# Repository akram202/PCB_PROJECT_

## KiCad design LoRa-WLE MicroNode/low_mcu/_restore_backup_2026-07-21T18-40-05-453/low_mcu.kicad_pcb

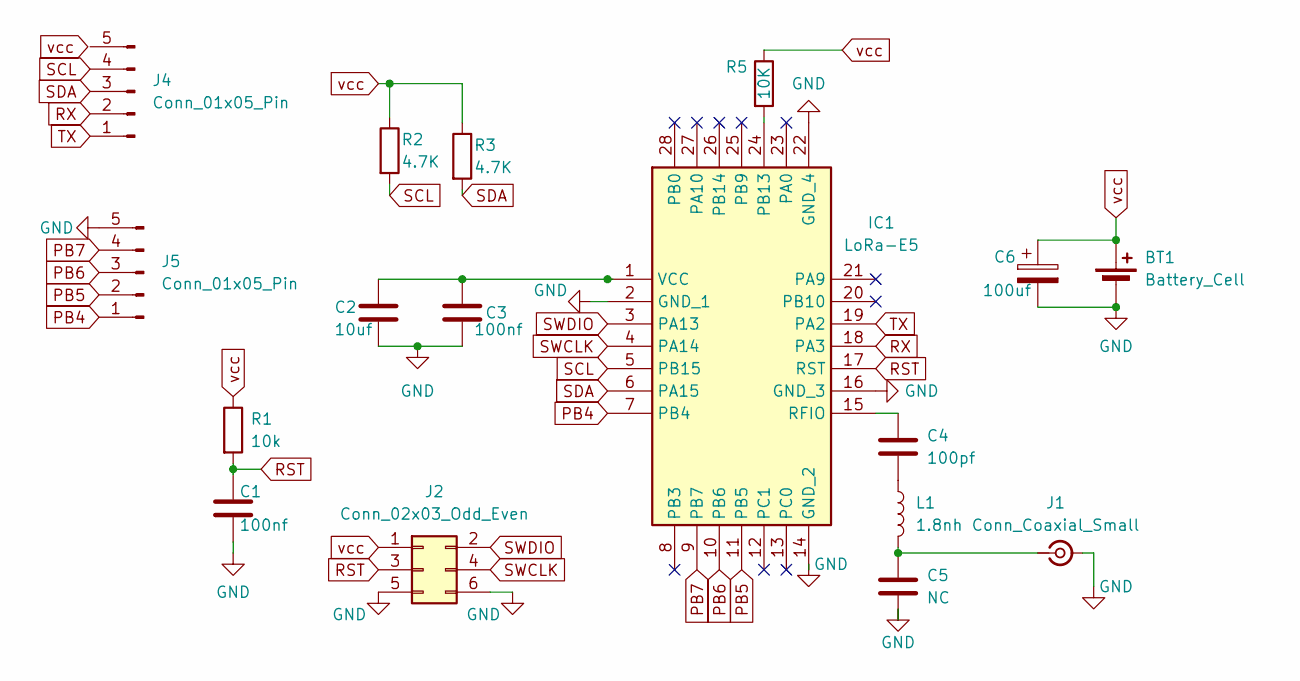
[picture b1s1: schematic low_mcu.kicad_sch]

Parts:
BT1: Battery_Cell; BatteryHolder_Keystone_3002_1x2032
C1, C3: 100nf; C_0402_1005Metric_Pad0.74x0.62mm_HandSolder
C2: 10uf; C_0603_1608Metric
C4: 100pf; C_0402_1005Metric
C5: NC; C_0402_1005Metric
C6: 100uf; CP_EIA-3528-21_Kemet-B
IC1: LoRa-E5; LoRaE5; Manufacturer_Part_Number LoRa-E5
J1: Conn_Coaxial_Small; U.FL_Hirose_U.FL-R-SMT-1_Vertical
J2: Conn_02x03_Odd_Even; Tag-Connect_TC2030-IDC-FP_2x03_P1.27mm_Vertical
J4, J5: Conn_01x05_Pin; PinHeader_1x05_P2.54mm_Vertical
L1: 1.8nh; L_0402_1005Metric
R1: 10k; R_0402_1005Metric
R2, R3: 4.7K; R_01005_0402Metric
R5: 10K; R_0402_1005Metric

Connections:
GND: BT1.2 (-), C1.2, C2.2, C3.2, C5.2, C6.2, IC1.2 (GND_1), IC1.14 (GND_2), IC1.16 (GND_3), IC1.22 (GND_4), J1.2 (Ext), J2.5, J2.6, J5.5
unnamed: C4.2, L1.1
unnamed: IC1.24 (PB13), R5.2
unnamed: C4.1, IC1.15 (RFIO)
unnamed: C2.1, C3.1, IC1.1 (VCC)
unnamed: C5.1, J1.1 (In), L1.2
PB4: IC1.7 (PB4), J5.1
PB5: IC1.11 (PB5), J5.2
PB6: IC1.10 (PB6), J5.3
PB7: IC1.9 (PB7), J5.4
RST: C1.1, IC1.17 (RST), J2.3, R1.2
RX: IC1.18 (PA3), J4.2
SCL: IC1.5 (PB15), J4.4, R2.2
SDA: IC1.6 (PA15), J4.3, R3.2
SWCLK: IC1.4 (PA14), J2.4
SWDIO: IC1.3 (PA13), J2.2
TX: IC1.19 (PA2), J4.1
vcc: BT1.1 (+), C6.1, J2.1, R1.1, R2.1, R3.1, R5.1

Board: 2 copper layers, 17 parts (0 on the bottom side), 18 nets, no tracks yet.

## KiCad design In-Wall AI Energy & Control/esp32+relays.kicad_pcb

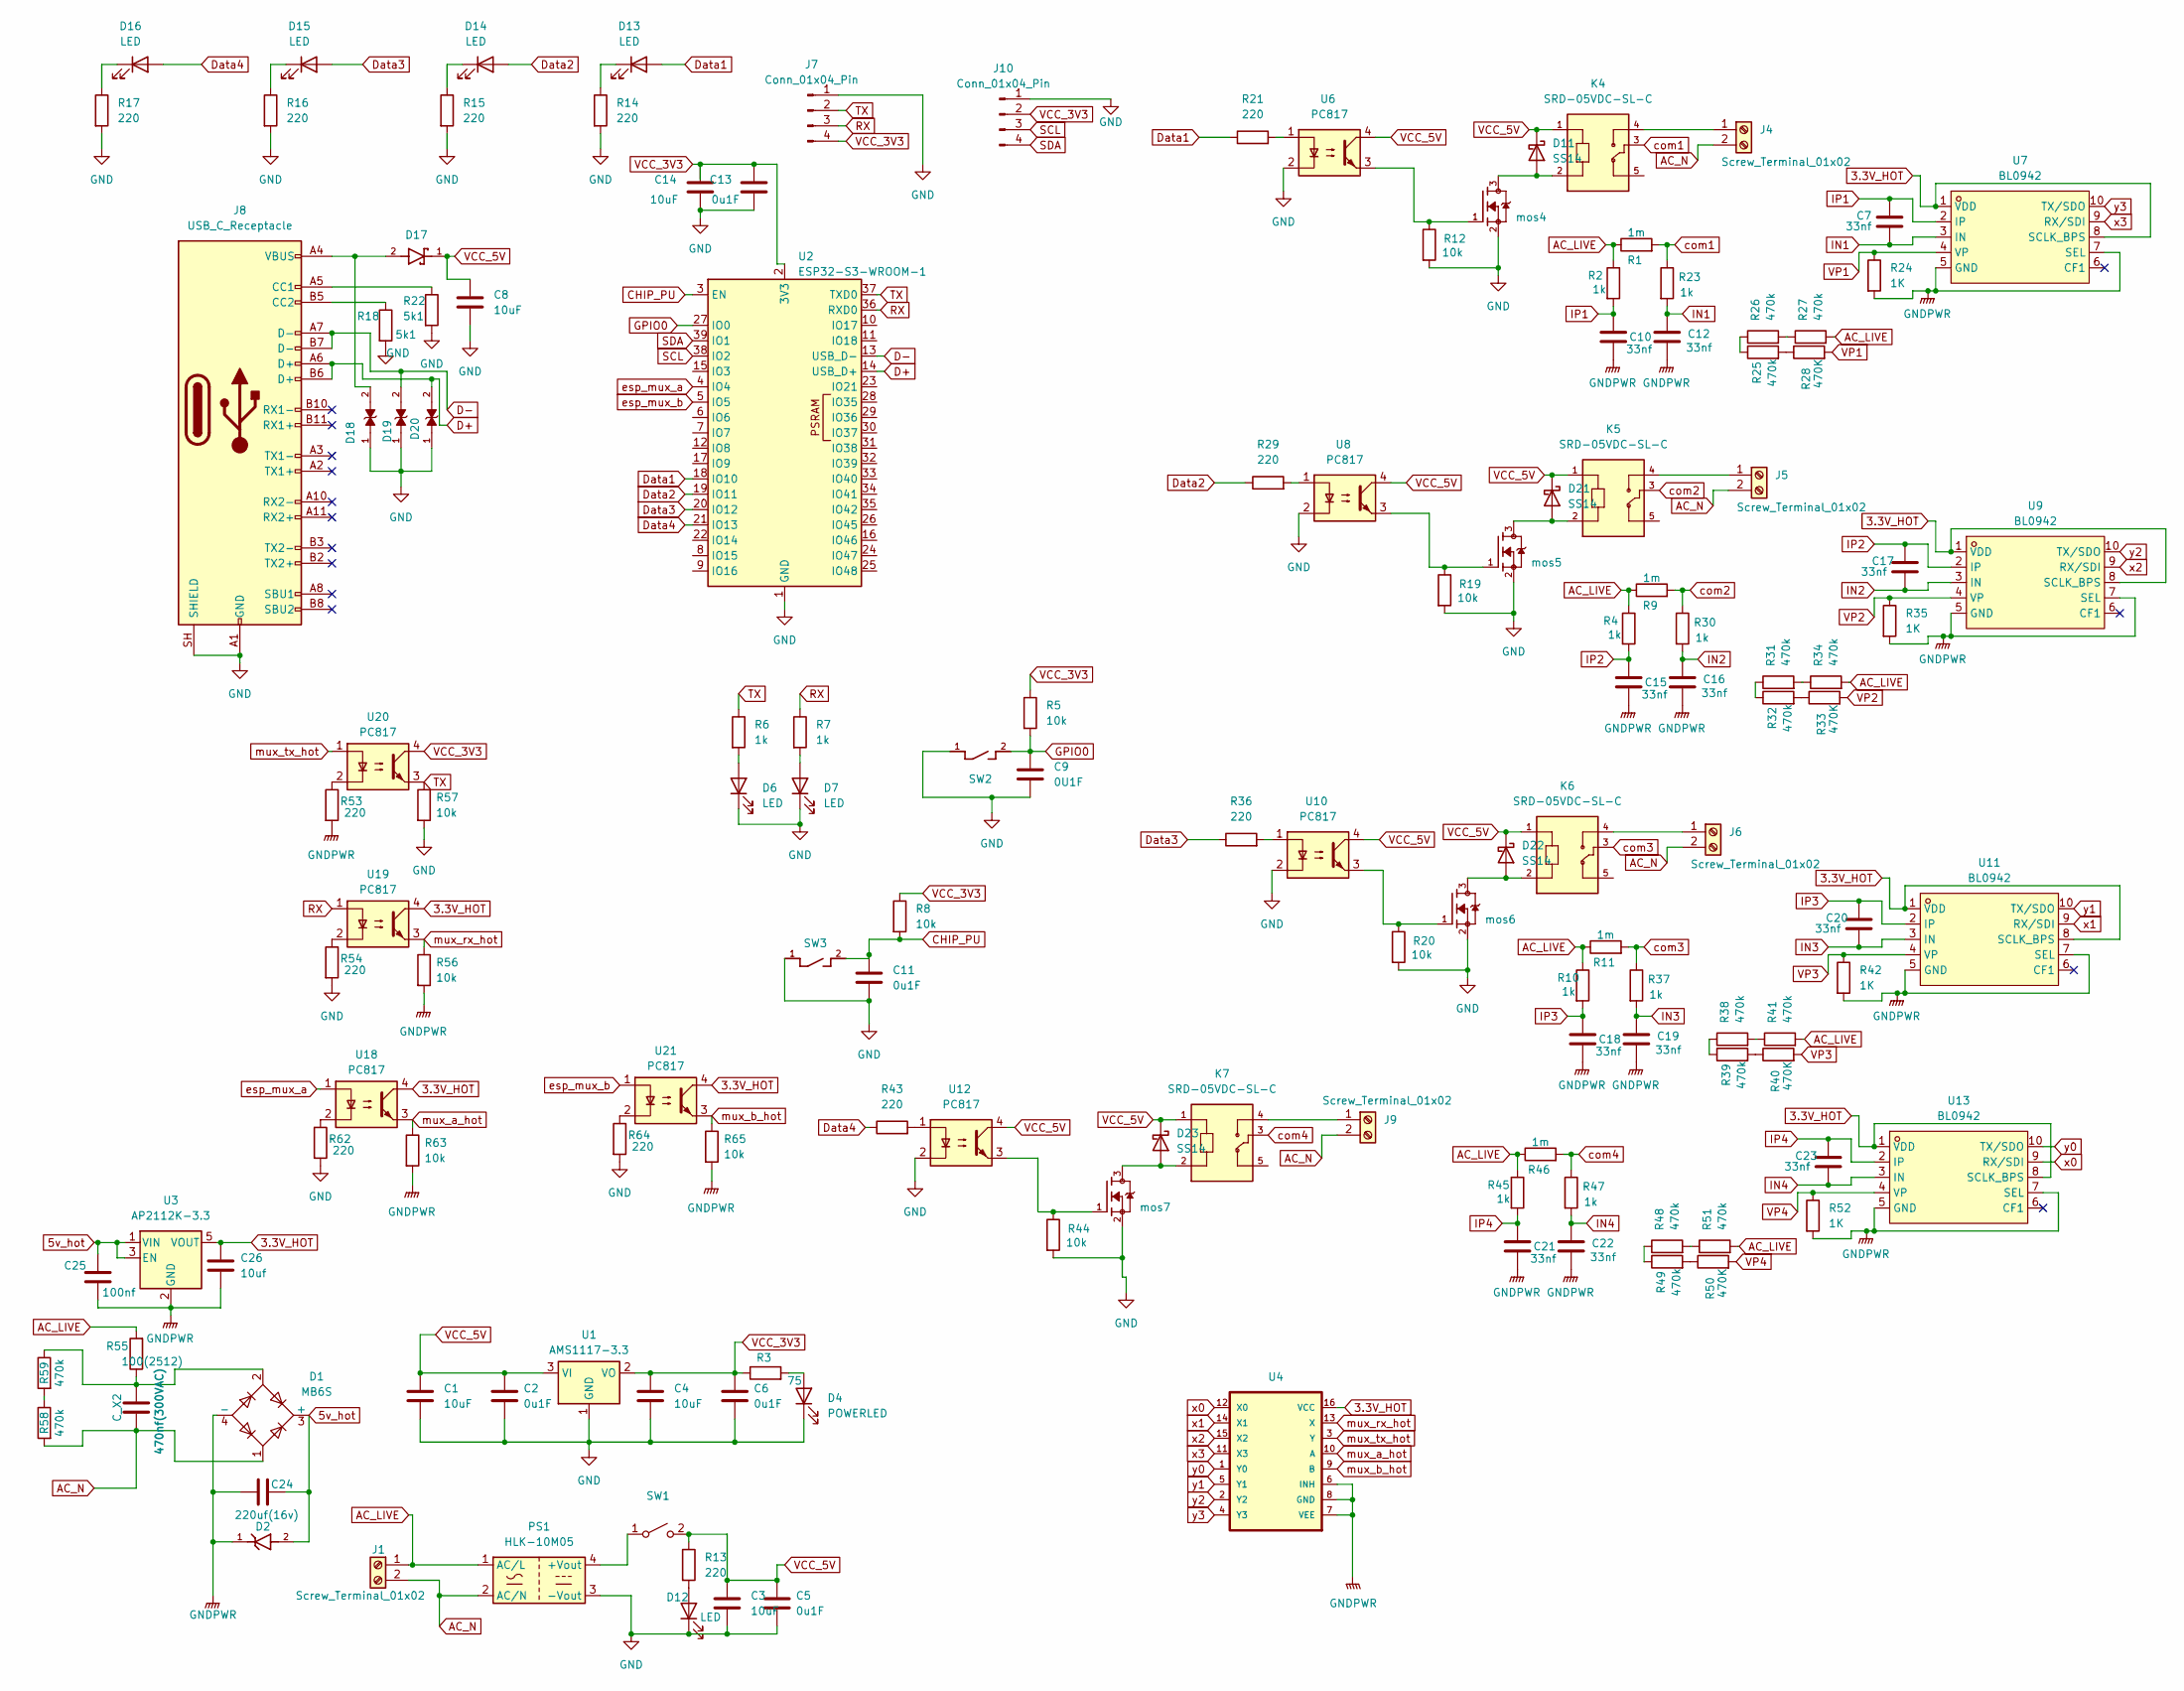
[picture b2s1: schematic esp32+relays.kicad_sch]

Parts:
C1, C3, C4, C8, C14: 10uF; C_0603_1608Metric
C2, C5, C6, C11, C13: 0u1F; C_0603_1608Metric
C7, C10, C12, C15, C16, C17, C18, C19, C20, C21, C22, C23: 33nf; C_0603_1608Metric
C9: 0U1F; C_0603_1608Metric
C24: 220uf(16v); C_1210_3225Metric
C25: 100nf; C_0805_2012Metric
C26: 10uf; C_0805_2012Metric
C_X2: 470nf(300VAC); C_Rect_L18.0mm_W7.0mm_P15.00mm_FKS3_FKP3
D1: MB6S; TO-269AA
D2: D_SMA; PARTREV 19 - 2
D4: POWERLED; LED_0201_0603Metric_Pad0.64x0.40mm_HandSolder
D6, D7: LED; LED_0603_1608Metric
D11, D21, D22, D23: SS14; D_SMA
D12, D13, D14, D15, D16: LED; LED_0201_0603Metric
D17: D_SOD-123; PARTREV 18-2
D18, D19, D20: D_SOD-523; PARTREV O
J1, J4, J5, J6, J9: Screw_Terminal_01x02; TerminalBlock_Phoenix_MKDS-1,5-2-5.08_1x02_P5.08mm_Horizont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
J7, J10: Conn_01x04_Pin; PinHeader_1x04_P2.54mm_Vertical
J8: USB_C_Receptacle; USB_C_Receptacle_Amphenol_12401548E4-2A
K4, K5, K6, K7: SRD-05VDC-SL-C; Relay_SPDT_SANYOU_SRD_Series_Form_C
PS1: HLK-10M05; Converter_ACDC_Hi-Link_HLK-10Mxx
R1, R9, R11, R46: 1m; R_2512_6332Metric
R2, R4, R10, R23, R30, R37, R45, R47: 1k; R_0805_2012Metric
R3: 75; R_0603_1608Metric
R5, R8, R12, R19, R20, R44: 10k; R_0603_1608Metric
R6, R7: 1k; R_0603_1608Metric
R13, R14, R15, R16, R17: 220; R_0603_1608Metric
R18, R22: 5k1; R_0603_1608Metric
R21, R29, R36, R43, R53, R54, R62, R64: 220; R_0805_2012Metric
R24, R35, R42, R52: 1K; R_0805_2012Metric
R25, R26, R27, R31, R32, R34, R38, R39, R41, R48, R49, R51, R58, R59: 470k; R_1206_3216Metric
R28, R33, R40, R50: 470K; R_1206_3216Metric
R55: 100(2512); R_2512_6332Metric
R56, R57: 10k; R_0805_2012Metric_Pad1.20x1.40mm_HandSolder
R63, R65: 10k; R_0805_2012Metric
SW1: SW_PUSH_6mm_H5mm
SW2: SW_SPST_PTS810
SW3: PTS810_SJM_250_SMTR_LFS; SW_SPST_PTS810
U1: AMS1117-3.3; SOT-223-3_TabPin2
U2: ESP32-S3-WROOM-1; ESP32-S3-WROOM-1U
U3: AP2112K-3.3; SOT-23-5
U4: 74HC4052; SO-16_3.9x9.9mm_P1.27mm
U6, U8, U10, U12, U18, U19, U20, U21: PC817; DIP-4_W7.62mm
U7, U9, U11, U13: BL0942; SSOP-10_3.9x4.9mm_P1.00mm; MPN BL0942; LCSC Part C2837510
mos4, mos5, mos6, mos7: SOT-23

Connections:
3.3V_HOT: C26.1, U3.5 (VOUT), U4.16 (VCC), U7.1 (VDD), U7.8 (SCLK_BPS), U9.1 (VDD), U9.8 (SCLK_BPS), U11.1 (VDD), U11.8 (SCLK_BPS), U13.1 (VDD), U13.8 (SCLK_BPS), U18.4, U19.4, U21.4
5v_hot: C24.2, C25.1, D1.3 (+), D2.2, U3.1 (VIN), U3.3 (EN)
AC_LIVE: J1.1, PS1.1 (AC/L), R1.1, R2.1, R4.1, R9.1, R10.1, R11.1, R27.2, R34.2, R41.2, R45.1, R46.1, R51.2, R55.2
AC_N: C_X2.1, D1.1, J1.2, J4.2, J5.2, J6.2, J9.2, PS1.2 (AC/N), R58.2
CHIP_PU: C11.1, R8.2, SW3.2, U2.3 (EN)
D+: D20.2, J8.A6 (D+), J8.B6 (D+), U2.14 (USB_D+)
D-: D19.2, J8.A7 (D-), J8.B7 (D-), U2.13 (USB_D-)
Data1: D13.2 (A), R21.1, U2.18 (IO10)
Data2: D14.2 (A), R29.1, U2.19 (IO11)
Data3: D15.2 (A), R36.1, U2.20 (IO12)
Data4: D16.2 (A), R43.1, U2.21 (IO13)
GND: C1.2, C2.2, C3.2, C4.2, C5.2, C6.2, C8.2, C9.2, C11.2, C13.2, C14.2, D4.1 (K), D6.1 (K), D7.1 (K), D12.1 (K), D18.1, D19.1, D20.1, J7.1, J8.A1 (GND), J8.A12 (GND), J8.B1 (GND), J8.B12 (GND), J8.SH (SHIELD), J10.1, PS1.3 (-Vout), R12.2, R14.2, R15.2, R16.2, R17.2, R18.2, R19.2, R20.2, R22.2, R44.2, R54.2, R57.2, R62.2, R64.2, SW2.1, SW3.1, U1.1 (GND), U2.1 (GND), U2.40 (GND), U2.41 (GND), U6.2, U8.2, U10.2, U12.2, mos4.2, mos5.2, mos6.2, mos7.2
GNDPWR: C10.2, C12.2, C15.2, C16.2, C18.2, C19.2, C21.2, C22.2, C24.1, C25.2, C26.2, D1.4 (-), D2.1, R24.2, R35.2, R42.2, R52.2, R53.2, R56.2, R63.2, R65.2, U3.2 (GND), U4.6 (INH), U4.7 (VEE), U4.8 (GND), U7.5 (GND), U7.7 (SEL), U9.5 (GND), U9.7 (SEL), U11.5 (GND), U11.7 (SEL), U13.5 (GND), U13.7 (SEL)
GPIO0: C9.1, R5.2, SW2.2, U2.27 (IO0)
IN1: C7.2, C12.1, R23.2, U7.3 (IN)
IN2: C16.1, C17.2, R30.2, U9.3 (IN)
IN3: C19.1, C20.2, R37.2, U11.3 (IN)
IN4: C22.1, C23.2, R47.2, U13.3 (IN)
IP1: C7.1, C10.1, R2.2, U7.2 (IP)
IP2: C15.1, C17.1, R4.2, U9.2 (IP)
IP3: C18.1, C20.1, R10.2, U11.2 (IP)
IP4: C21.1, C23.1, R45.2, U13.2 (IP)
unnamed: C_X2.2, D1.2, R55.1, R59.1
unnamed: D4.2 (A), R3.2
unnamed: D6.2 (A), R6.2
unnamed: D7.2 (A), R7.2
unnamed: D11.2 (A), K4.2, mos4.3
unnamed: D12.2 (A), R13.2
unnamed: D13.1 (K), R14.1
unnamed: D14.1 (K), R15.1
unnamed: D15.1 (K), R16.1
unnamed: D16.1 (K), R17.1
unnamed: D17.2, D18.2, J8.A4 (VBUS), J8.A9 (VBUS), J8.B4 (VBUS), J8.B9 (VBUS)
unnamed: D21.2 (A), K5.2, mos5.3
unnamed: D22.2 (A), K6.2, mos6.3
unnamed: D23.2 (A), K7.2, mos7.3
unnamed: J4.1, K4.4
unnamed: J5.1, K5.4
unnamed: J6.1, K6.4
unnamed: J8.A5 (CC1), R22.1
unnamed: J8.B5 (CC2), R18.1
unnamed: J9.1, K7.4
unnamed: PS1.4 (+Vout), SW1.1 (A)
unnamed: R12.1, U6.3, mos4.1
unnamed: R19.1, U8.3, mos5.1
unnamed: R20.1, U10.3, mos6.1
unnamed: R21.2, U6.1
unnamed: R25.1, R26.1
unnamed: R25.2, R28.1
unnamed: R26.2, R27.1
unnamed: R29.2, U8.1
unnamed: R31.1, R32.1
unnamed: R31.2, R34.1
unnamed: R32.2, R33.1
unnamed: R36.2, U10.1
unnamed: R38.1, R39.1
unnamed: R38.2, R41.1
unnamed: R39.2, R40.1
unnamed: R43.2, U12.1
unnamed: R44.1, U12.3, mos7.1
unnamed: R48.1, R49.1
unnamed: R48.2, R51.1
unnamed: R49.2, R50.1
unnamed: R53.1, U20.2
unnamed: R54.1, U19.2
unnamed: R58.1, R59.2
unnamed: R62.1, U18.2
unnamed: R64.1, U21.2
RX: J7.3, R7.1, U2.36 (RXD0), U19.1
SCL: J10.3, U2.38 (IO2)
SDA: J10.4, U2.39 (IO1)
TX: J7.2, R6.1, R57.1, U2.37 (TXD0), U20.3
VCC_3V3: C4.1, C6.1, C13.1, C14.1, J7.4, J10.2, R3.1, R5.1, R8.1, U1.2 (VO), U2.2 (3V3), U20.4
VCC_5V: C1.1, C2.1, C3.1, C5.1, C8.1, D11.1 (K), D17.1, D21.1 (K), D22.1 (K), D23.1 (K), K4.1, K5.1, K6.1, K7.1, R13.1, SW1.2 (B), U1.3 (VI), U6.4, U8.4, U10.4, U12.4
VP1: R24.1, R28.2, U7.4 (VP)
VP2: R33.2, R35.1, U9.4 (VP)
VP3: R40.2, R42.1, U11.4 (VP)
VP4: R50.2, R52.1, U13.4 (VP)
com1: K4.3, R1.2, R23.1
com2: K5.3, R9.2, R30.1
com3: K6.3, R11.2, R37.1
com4: K7.3, R46.2, R47.1
esp_mux_a: U2.4 (IO4), U18.1
esp_mux_b: U2.5 (IO5), U21.1
mux_a_hot: R63.1, U4.10 (A), U18.3
mux_b_hot: R65.1, U4.9 (B), U21.3
mux_rx_hot: R56.1, U4.13 (X), U19.3
mux_tx_hot: U4.3 (Y), U20.1
x0: U4.12 (X0), U13.9 (RX/SDI)
x1: U4.14 (X1), U11.9 (RX/SDI)
x2: U4.15 (X2), U9.9 (RX/SDI)
x3: U4.11 (X3), U7.9 (RX/SDI)
y0: U4.1 (Y0), U13.10 (TX/SDO)
y1: U4.5 (Y1), U11.10 (TX/SDO)
y2: U4.2 (Y2), U9.10 (TX/SDO)
y3: U4.4 (Y3), U7.10 (TX/SDO)

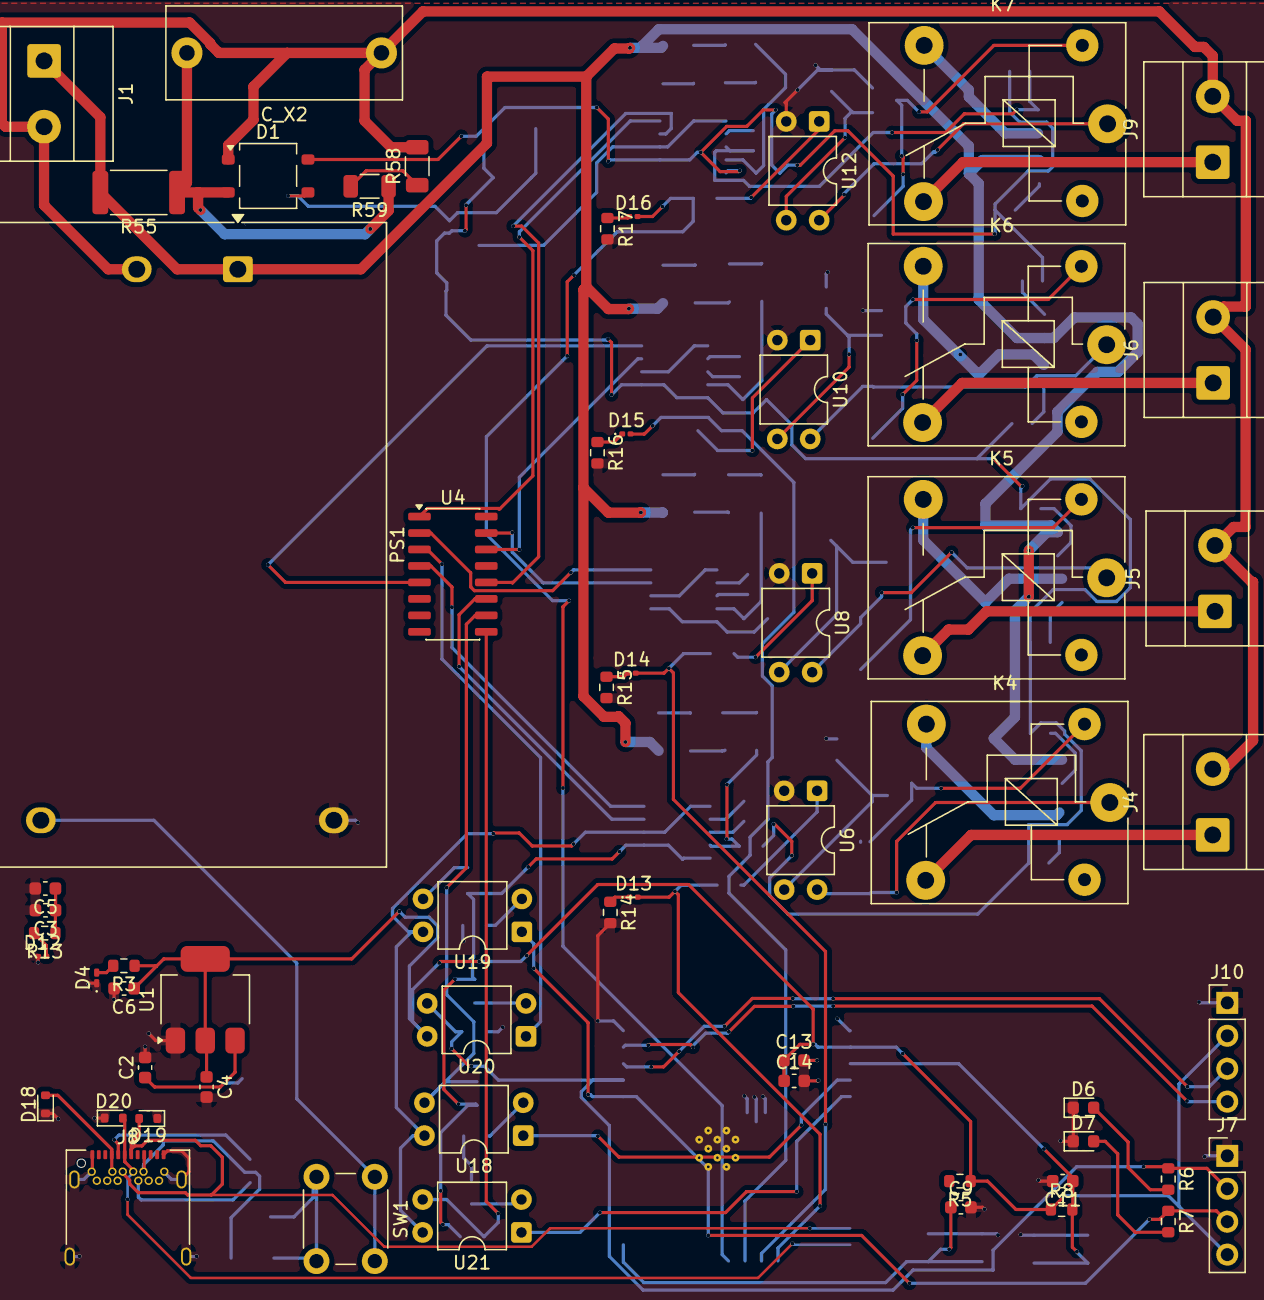
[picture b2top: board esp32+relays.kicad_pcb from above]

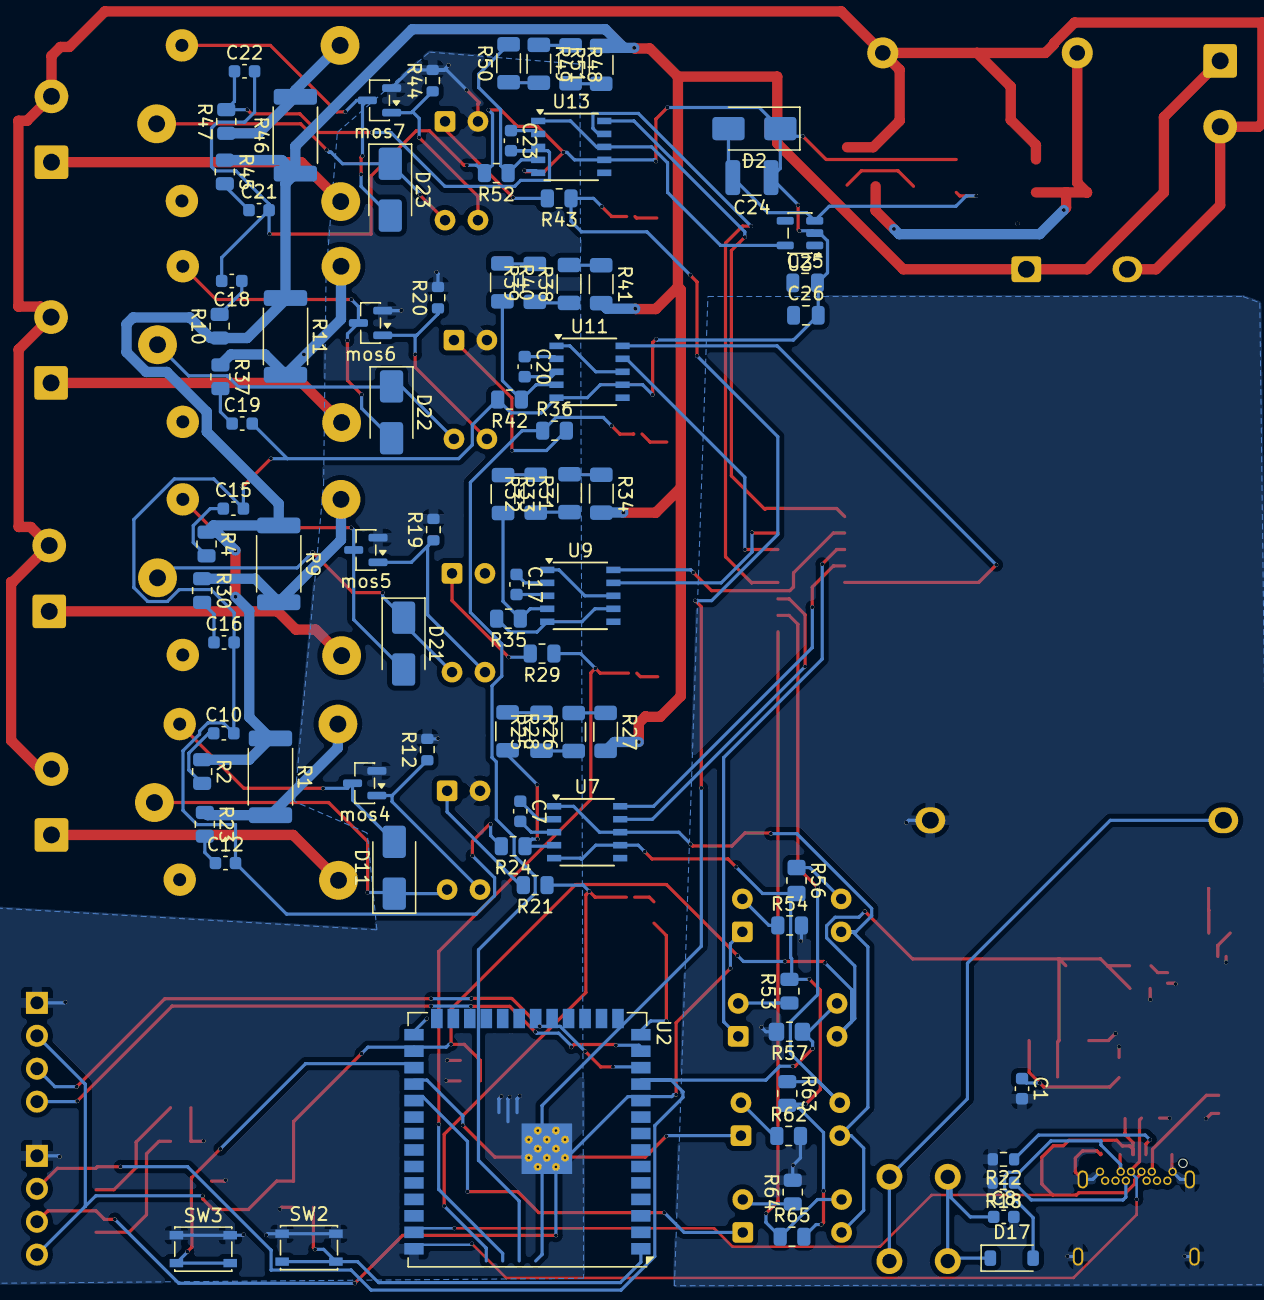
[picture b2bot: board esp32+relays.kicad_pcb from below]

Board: 2 copper layers, 144 parts (85 on the bottom side), 96 nets.

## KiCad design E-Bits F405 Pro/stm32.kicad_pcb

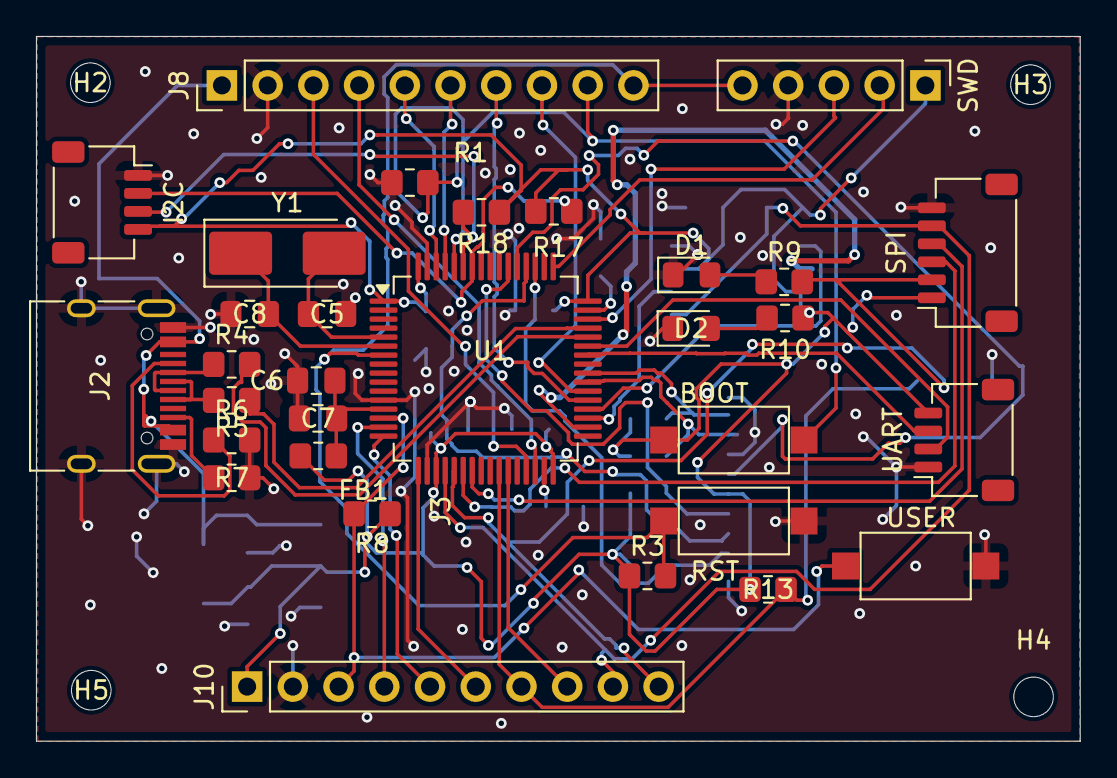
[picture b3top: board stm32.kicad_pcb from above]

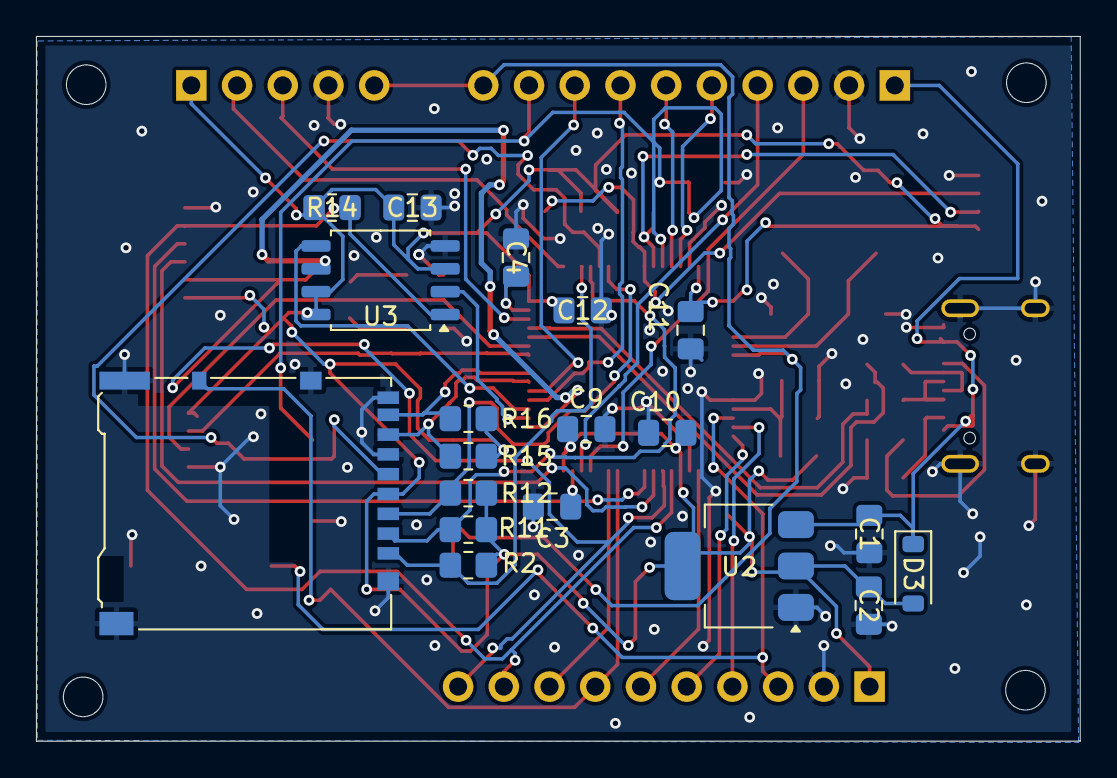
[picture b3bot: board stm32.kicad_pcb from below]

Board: 2 copper layers, 58.0 x 39.1 mm, 54 parts (19 on the bottom side), 49 nets.

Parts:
BOOT: SW_Push; SW_SPST_CK_RS282G05A3
C1, C2: 10uf; C_0805_2012Metric_Pad1.18x1.45mm_HandSolder
C3, C4: 2.2uf; C_0805_2012Metric_Pad1.18x1.45mm_HandSolder
C5, C8: 22pf; C_0805_2012Metric_Pad1.18x1.45mm_HandSolder
C6: 1uf; C_0805_2012Metric_Pad1.18x1.45mm_HandSolder
C7: 10nf; C_0805_2012Metric_Pad1.18x1.45mm_HandSolder
C9, C10, C11, C12, C13: 100nf; C_0805_2012Metric_Pad1.18x1.45mm_HandSolder
D1, D2: LED; LED_0805_2012Metric_Pad1.15x1.40mm_HandSolder
D3: 1N5819; D_SOD-123
FB1: FerriteBead; R_0805_2012Metric_Pad1.20x1.40mm_HandSolder
H2, H3, H4, H5: MountingHole; MountingHole_2.2mm_M2
I2C: Conn_01x04_Pin; JST_SH_SM04B-SRSS-TB_1x04-1MP_P1.00mm_Horizontal
J2: USB_C_Receptacle_USB2.0_14P; USB_C_Receptacle_HRO_TYPE-C-31-M-12
J3: Micro_SD_Card_Det_Hirose_DM3AT; microSD_HC_Hirose_DM3AT-SF-PEJM5
J8, J10: Conn_01x10_Pin; PinHeader_1x10_P2.54mm_Vertical
R1, R8: R; R_0805_2012Metric_Pad1.20x1.40mm_HandSolder
R2, R3, R11, R12, R13, R14, R15, R16: 10k; R_0805_2012Metric_Pad1.20x1.40mm_HandSolder
R4, R5: 22; R_0805_2012Metric_Pad1.20x1.40mm_HandSolder
R6, R7: 5.1k; R_0805_2012Metric_Pad1.20x1.40mm_HandSolder
R9, R10: 330; R_0805_2012Metric_Pad1.20x1.40mm_HandSolder
R17: 4.7k; R_0805_2012Metric_Pad1.20x1.40mm_HandSolder
R18: 4,7k; R_0805_2012Metric_Pad1.20x1.40mm_HandSolder
RST: SW_Push; SW_SPST_CK_RS282G05A3
SPI: Conn_01x06_Pin; JST_SH_SM06B-SRSS-TB_1x06-1MP_P1.00mm_Horizontal
SWD: Conn_01x05_Pin; PinHeader_1x05_P2.54mm_Vertical
U1: STM32F405RGTx; LQFP-64_10x10mm_P0.5mm
U2: AMS1117-3.3; SOT-223-3_TabPin2
U3: W25Q128JVS; SOIC-8_5.3x5.3mm_P1.27mm
UART: Conn_01x04_Pin; JST_SH_SM04B-SRSS-TB_1x04-1MP_P1.00mm_Horizontal
USER: SW_Push; SW_SPST_CK_RS282G05A3
Y1: Crystal; Crystal_SMD_5032-2Pin_5.0x3.2mm_HandSoldering

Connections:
3.3v: BOOT.1, C2.1, C9.1, C10.1, C11.1, C12.1, C13.1, D3.2 (A), FB1.1, I2C.4, J3.4 (VDD), J10.1, R2.2, R3.1, R8.1, R10.2, R11.2, R12.2, R13.2, R14.1, R15.2, R16.2, R17.1, R18.1, SPI.1, SWD.1, U1.1 (VBAT), U1.19 (VDD), U1.32 (VDD), U1.48 (VDD), U1.64 (VDD), U2.2 (VO), U3.3 (~WP/IO_{2}), U3.7 (~HOLD/~RESET/IO_{3}), U3.8 (VCC), UART.4
5V: C1.1, D3.1 (K), J2.A4 (VBUS), J2.A9 (VBUS), J2.B4 (VBUS), J2.B9 (VBUS), J8.1, U2.3 (VI)
BOOT: BOOT.2, J8.9, R1.1, U1.60 (BOOT0)
CLK: J3.5 (CLK), U1.53 (PC12)
CLK_s: U1.34 (PB13), U3.6 (CLK)
CMD: J3.3 (CMD), R12.1, U1.54 (PD2)
D0: U1.35 (PB14), U3.2 (DO/IO_{1})
D1: U1.36 (PB15), U3.5 (DI/IO_{0})
D+: R5.2, U1.45 (PA12)
D-: R4.2, U1.44 (PA11)
DAT0: J3.7 (DAT0), R15.1, U1.39 (PC8)
DAT1: J3.8 (DAT1), R16.1, U1.40 (PC9)
DAT2: J3.1 (DAT2), R2.1, U1.51 (PC10)
DAT3: J3.2 (DAT3/CD), R11.1, U1.52 (PC11)
GND: C1.2, C2.2, C3.1, C4.2, C5.1, C6.2, C7.2, C8.2, C9.2, C10.2, C11.2, C12.2, C13.2, D1.1 (K), D2.1 (K), I2C.1, J2.A1 (GND), J2.A12 (GND), J2.B1 (GND), J2.B12 (GND), J2.S1 (SHIELD), J3.6 (VSS), J3.9 (DET_B), J3.11 (SHIELD), J8.2, J10.2, R1.2, R6.2, R7.2, RST.1, SPI.6, SWD.4, U1.12 (VSSA), U1.18 (VSS), U1.63 (VSS), U2.1 (GND), U3.4 (GND), UART.1, USER.2
NRST: J8.10, R3.2, RST.2, SWD.5, U1.7 (NRST)
unnamed: D1.2 (A), R9.1
unnamed: D2.2 (A), R10.1
unnamed: J2.A5 (CC1), R6.1
unnamed: J2.B5 (CC2), R7.1
unnamed: J2.A6 (D+), J2.B6 (D+), R5.1
unnamed: J2.A7 (D-), J2.B7 (D-), R4.1
unnamed: C5.2, U1.5 (PH0), Y1.2
unnamed: C8.1, U1.6 (PH1), Y1.1
PA0: J10.3, R8.2, U1.14 (PA0), USER.1
PA1: J10.4, U1.15 (PA1)
PA2: J10.5, U1.16 (PA2)
PA3: J10.6, U1.17 (PA3)
PA4: J10.9, R14.2, SPI.5, U1.20 (PA4), U3.1 (~CS)
PA5: J10.10, R9.2, SPI.2, U1.21 (PA5)
PA6: SPI.3, U1.22 (PA6)
PA7: SPI.4, U1.23 (PA7)
PA9: U1.42 (PA9), UART.3
PA10: U1.43 (PA10), UART.2
PB0: J3.10 (DET_A), J10.7, R13.1, U1.26 (PB0)
PB1: J10.8, U1.27 (PB1)
PB6: I2C.2, R17.2, U1.58 (PB6)
PB7: I2C.3, R18.2, U1.59 (PB7)
PB8: J8.6, U1.61 (PB8)
PB9: J8.5, U1.62 (PB9)
PB10: J8.3, U1.29 (PB10)
PB11: J8.4, U1.30 (PB11)
PC6: J8.7, U1.37 (PC6)
PC7: J8.8, U1.38 (PC7)
SWCLK: SWD.2, U1.49 (PA14)
SWDIO: SWD.3, U1.46 (PA13)
VDDA: C6.1, C7.1, FB1.2, U1.13 (VDDA)
V_cap1: C3.2, U1.31 (VCAP_1)
V_cap2: C4.1, U1.47 (VCAP_2)

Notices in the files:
parts and their libraries:
COPYRIGHT: Copyright (C) 2023 Ultra Librarian. All rights reserved.
